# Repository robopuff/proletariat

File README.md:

# Proletariat

Easy to build, pro-micro (nice!nano for bluetooth) through the hole
numpad/macropad with rotary encoders and 0.91" OLED support.

## Required components

- 24 or 25x 1N4148 axial diodes
  - 25 if battery pack and on/off switch included
- 1x tactile switch (reset)
- 1x slide switch (on/off, 450302014072-ND recommended)
- Battery holder and 3.3V rechargable battery
- 2xEC12/EC16 Rotary Encoders with knobs (Kilo International for the ultimate look and feel)
- Pro Micro compatible MCU
  - For BT use nice!nano
  - For anything else, do not connect battery pack, or check pinouts for further compatibility
- One or none of the supported OLED screens
  - 0.91" SSD1306 I2C OLED
- 27x  Kailh hot swappable sockets
- 24x MX-compatible switches & keycaps
  - Supports 3x2u

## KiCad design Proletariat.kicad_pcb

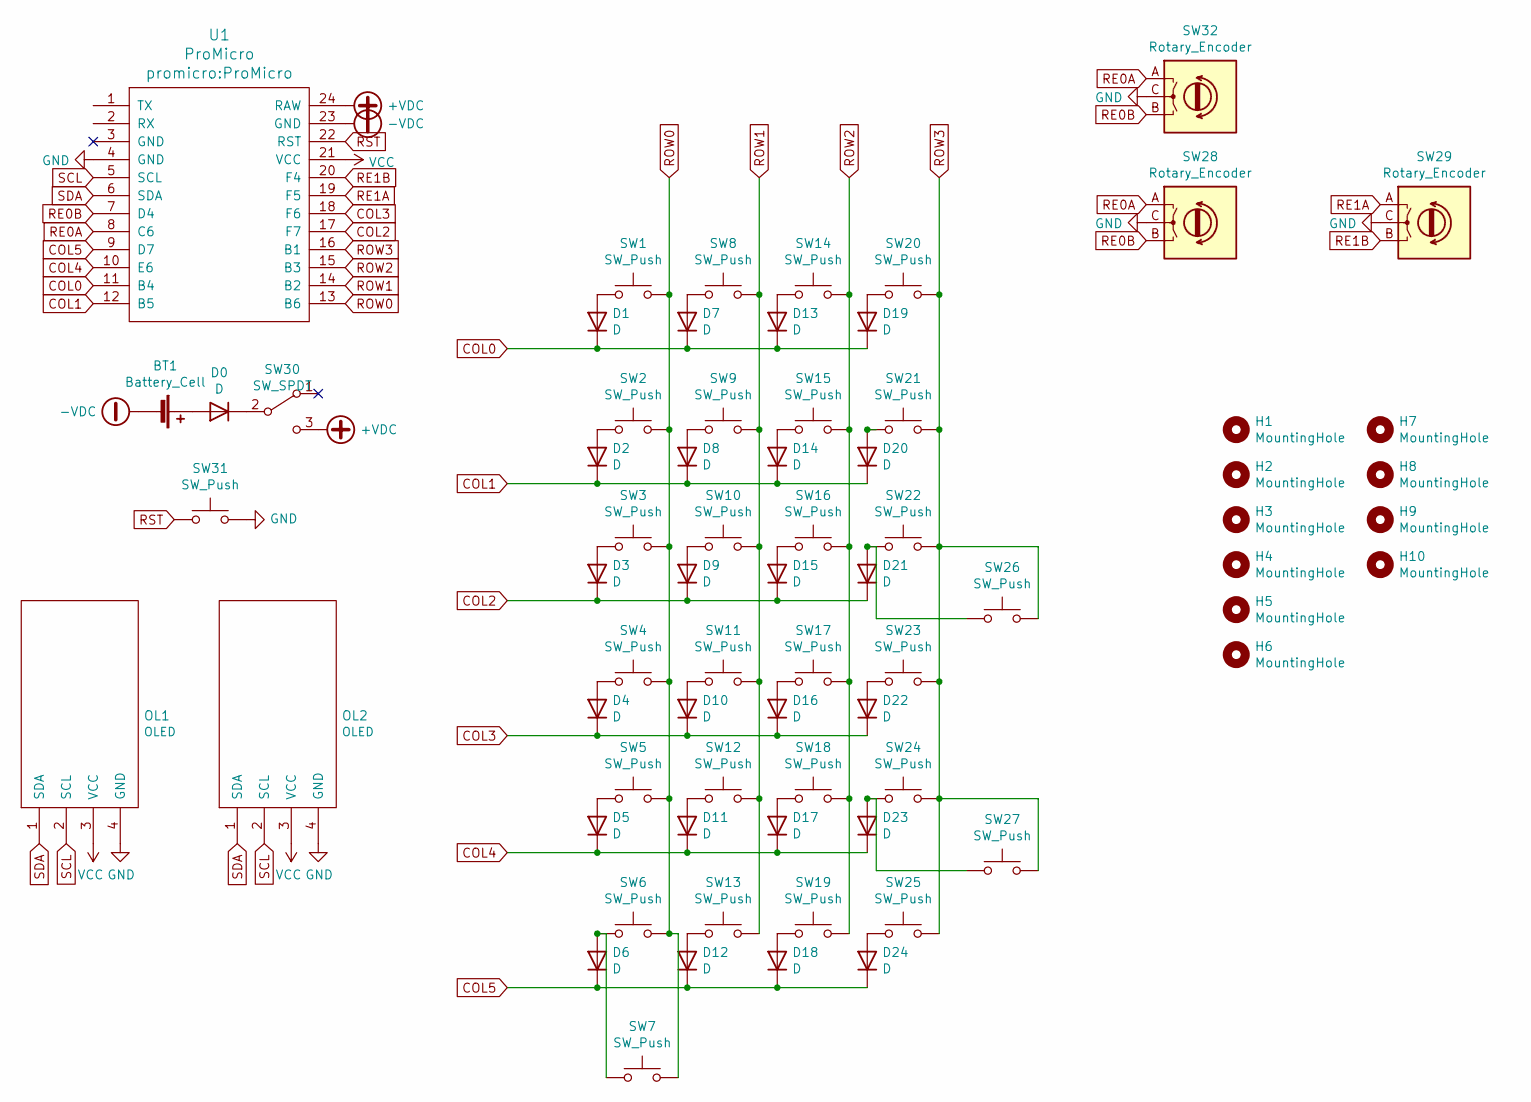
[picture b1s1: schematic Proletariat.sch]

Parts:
BT1: Battery_Cell; BatteryHolder_MPD_BH-18650-PC2
D0, D1, D2, D3, D4, D5, D6, D7, D8, D9, D10, D11, D12, D13, D14, D15, D16, D17, D18, D19, D20, D21, D22, D23, D24: D; Diode_keyboard
H1, H2, H3, H4, H5, H6, H7, H8, H9, H10: MountingHole; Generic-Mounthole
OL1, OL2: OLED; OLED_v2
SW1, SW2, SW3, SW4, SW5, SW6, SW8, SW9, SW10, SW11, SW12, SW13, SW14, SW15, SW16, SW17, SW18, SW19, SW20, SW21, SW22, SW23, SW24, SW25: SW_Push; SW_Hotswap_Kailh_1.00u
SW7: SW_Push; SW_Hotswap_Kailh_2.00u
SW26, SW27: SW_Push; SW_Hotswap_Kailh_2.00u_Rotated
SW28, SW29: Rotary_Encoder; RotaryEncoder_Alps_EC12E_Vertical_H20mm
SW30: SW_SPDT; SW_SLIDE_SPDT_HORIZONTAL; Part Wurth Elektronik 450301014042; DigiKey 450301014042-ND
SW31: SW_Push; SW_PUSH_6mm_H4.3mm
SW32: Rotary_Encoder; RotaryEncoder_Alps_EC12E_Vertical_H20mm_CircularMountingHol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
U1: ProMicro

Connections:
+VDC: SW30.3 (C), U1.24 (RAW)
-VDC: BT1.2 (-), U1.23 (GND)
COL0: D1.1 (K), D7.1 (K), D13.1 (K), D19.1 (K), U1.11 (B4)
COL1: D2.1 (K), D8.1 (K), D14.1 (K), D20.1 (K), U1.12 (B5)
COL2: D3.1 (K), D9.1 (K), D15.1 (K), D21.1 (K), U1.17 (F7)
COL3: D4.1 (K), D10.1 (K), D16.1 (K), D22.1 (K), U1.18 (F6)
COL4: D5.1 (K), D11.1 (K), D17.1 (K), D23.1 (K), U1.10 (E6)
COL5: D6.1 (K), D12.1 (K), D18.1 (K), D24.1 (K), U1.9 (D7)
GND: OL1.4 (GND), OL2.4 (GND), SW28.C, SW29.C, SW31.2, SW32.C, U1.4 (GND)
unnamed: BT1.1 (+), D0.2 (A)
unnamed: D0.1 (K), SW30.2 (B)
unnamed: D1.2 (A), SW1.1
unnamed: D2.2 (A), SW2.1
unnamed: D3.2 (A), SW3.1
unnamed: D4.2 (A), SW4.1
unnamed: D5.2 (A), SW5.1
unnamed: D6.2 (A), SW6.1, SW7.1
unnamed: D7.2 (A), SW8.1
unnamed: D8.2 (A), SW9.1
unnamed: D9.2 (A), SW10.1
unnamed: D10.2 (A), SW11.1
unnamed: D11.2 (A), SW12.1
unnamed: D12.2 (A), SW13.1
unnamed: D13.2 (A), SW14.1
unnamed: D14.2 (A), SW15.1
unnamed: D15.2 (A), SW16.1
unnamed: D16.2 (A), SW17.1
unnamed: D17.2 (A), SW18.1
unnamed: D18.2 (A), SW19.1
unnamed: D19.2 (A), SW20.1
unnamed: D20.2 (A), SW21.1
unnamed: D21.2 (A), SW22.1, SW26.1
unnamed: D22.2 (A), SW23.1
unnamed: D23.2 (A), SW24.1, SW27.1
unnamed: D24.2 (A), SW25.1
RE0A: SW28.A, SW32.A, U1.8 (C6)
RE0B: SW28.B, SW32.B, U1.7 (D4)
RE1A: SW29.A, U1.19 (F5)
RE1B: SW29.B, U1.20 (F4)
ROW0: SW1.2, SW2.2, SW3.2, SW4.2, SW5.2, SW6.2, SW7.2, U1.13 (B6)
ROW1: SW8.2, SW9.2, SW10.2, SW11.2, SW12.2, SW13.2, U1.14 (B2)
ROW2: SW14.2, SW15.2, SW16.2, SW17.2, SW18.2, SW19.2, U1.15 (B3)
ROW3: SW20.2, SW21.2, SW22.2, SW23.2, SW24.2, SW25.2, SW26.2, SW27.2, U1.16 (B1)
RST: SW31.1, U1.22 (RST)
SCL: OL1.2 (SCL), OL2.2 (SCL), U1.5 (SCL)
SDA: OL1.1 (SDA), OL2.1 (SDA), U1.6 (SDA)
VCC: OL1.3 (VCC), OL2.3 (VCC), U1.21 (VCC)

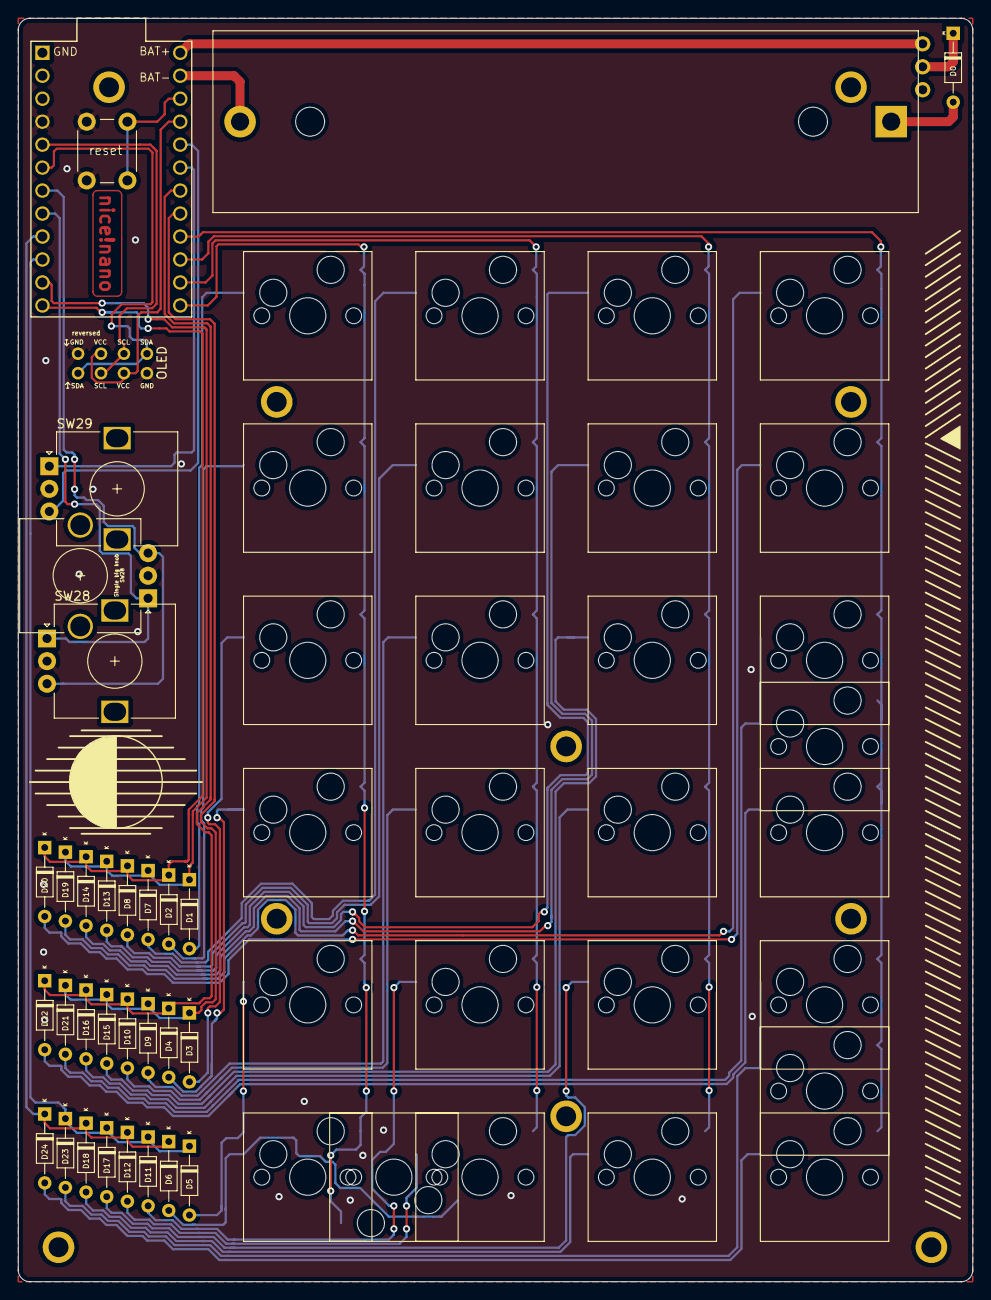
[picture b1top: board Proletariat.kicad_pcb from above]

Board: 2 copper layers, 105.5 x 139.7 mm, 71 parts (1 on the bottom side), 47 nets.

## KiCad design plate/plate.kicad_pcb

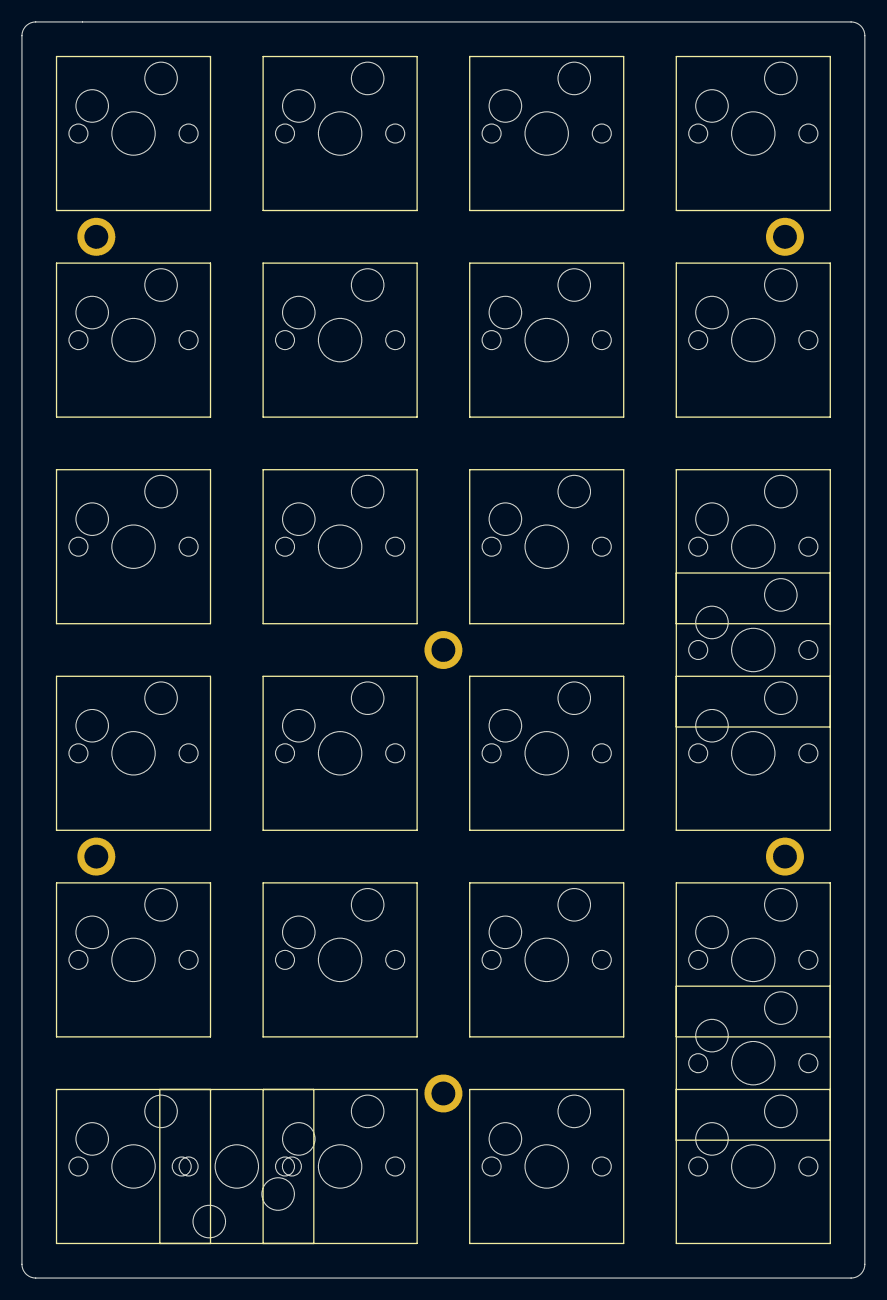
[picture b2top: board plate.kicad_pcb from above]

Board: 2 copper layers, 77.7 x 115.8 mm, 33 parts (0 on the bottom side), 7 nets, no tracks yet.

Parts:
H2, H5, H7, H8, H9, H10: MountingHole; Generic-Mounthole
SW1, SW2, SW3, SW4, SW5, SW6, SW8, SW9, SW10, SW11, SW12, SW13, SW14, SW15, SW16, SW17, SW18, SW19, SW20, SW21, SW22, SW23, SW24, SW25: SW_Push; SW_Hotswap_Kailh_1.00u
SW7: SW_Push; SW_Hotswap_Kailh_2.00u
SW26, SW27: SW_Push; SW_Hotswap_Kailh_2.00u_Rotated

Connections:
unnamed: SW6.1, SW7.1
unnamed: SW22.1, SW26.1
unnamed: SW24.1, SW27.1
ROW0: SW1.2, SW2.2, SW3.2, SW4.2, SW5.2, SW6.2, SW7.2
ROW1: SW8.2, SW9.2, SW10.2, SW11.2, SW12.2, SW13.2
ROW2: SW14.2, SW15.2, SW16.2, SW17.2, SW18.2, SW19.2
ROW3: SW20.2, SW21.2, SW22.2, SW23.2, SW24.2, SW25.2, SW26.2, SW27.2

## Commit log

2021-10-29 first version
2021-10-29 add libs
2021-10-29 update docs
2021-10-29 remove unnecessary gerber zip files
